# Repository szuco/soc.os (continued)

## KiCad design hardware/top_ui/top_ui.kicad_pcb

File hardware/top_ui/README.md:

# TOP – Front / UI

KiCad-Projekt `top_ui`. Bedien- und Sensorikebene des Stacks, zur Front orientiert.

## Umfang

Bestückt sind 29 Bauteile, 53 Netze (`bom_top.csv`):

- **USB-C-Buchse, stehend** (G-Switch GT-USB-7051x, vertikal SMT) — zeigt nach
  vorn und liegt unter der Zentralscheibe, mit **USBLC6-2SC6** als ESD-Schutz
  und 2 × 5k1 Rd
- **Runddisplay ST77916**, 1,46", 360 × 360, QSPI — über eine Steckerleiste;
  der Footprint ist ein **Platzhalter**, bis das reale Modul mit seinem FPC
  vermessen ist
- **Vier SMD-Taster** auf (±18 · ±20), exakt unter den Druckkreuzen der
  Zentralscheibe. Einzeln bedeuten sie nichts — jede Bedienrichtung ist ein
  Paar benachbarter Ecken, aufgelöst in der Firmware
- **SHT40-AD1B** (0x44) für Temperatur und Feuchte, thermisch über Schlitze
  entkoppelt
- **VL53L1X** als Präsenz- und Durchstiegssensor hinter dem **oberen** Steg
  (12 Uhr), XSHUT über 10k dauerhaft aktiv
- **Stern-Ausgang** über P-FET-High-Side und 0,2-A-PTC auf eine
  2,5-mm-Klinkenbuchse im **unteren** Steg (6 Uhr, Footprint noch Platzhalter,
  Punkt 30)
- `J7` als **unbestückte Reserve-UART** für ein späteres Satellitenmodul
- Stackverbinder `J_STK_A` und `J_STK_B` nach unten

Ein USB-UART-Baustein entfällt — der ESP32-S3 hat nativen USB (Punkt 24).

## Kernregeln

- **USB `D+`/`D−` laufen durch den Stack** (`J_STK_A` 34/36, benachbart, PGND
  daneben). Das ist die Regeländerung v0.3 in
  [`docs/03-stack-pinout.md`](../../docs/03-stack-pinout.md): Mit dem nativen USB
  des ESP32-S3 auf dem **Mid**-Board gibt es keine Alternative, und Full-Speed-USB
  über zwei benachbarte Kontakte ist unkritisch.
- ESD-Schutz unmittelbar an der USB-C-Buchse, `D+`/`D−` kurz führen.
- USB-C bleibt **Device/UFP**: `CC1` und `CC2` jeweils einzeln mit 5,1 kΩ Rd nach GND.
- Der Stern-Ausgang wird aus `6V2_STAR` über den Stack versorgt und leuchtet damit nur im
  24-V-Normalbetrieb — **nicht** aus USB-VBUS speisen.

## Mechanik

- **47 × 47 mm mit R 4**, 1,0 mm Dicke — als einziges Board nicht rund
- Bohrbild und Stackverbinder-Positionen **deckungsgleich** mit BOTTOM und MID
- Das Board ist **quadratisch, 47 × 47 mm mit R 4** — als einziges der drei.
  Es sitzt vor der Dose im Adapter, weil die Druckkreuze der Zentralscheibe auf
  r = 26,9 liegen und ein Kreis dort nicht hinreicht. Geometrie und Tiefenkette:
  [`mechanical/adapter.py`](../../mechanical/adapter.py)
- Frontorientierung: mathematisch +Y = „oben“, identisch auf allen drei Boards

Exakte Koordinaten: [`../../docs/04-mechanical.md`](../../docs/04-mechanical.md)

## Referenzdokumente

- [`docs/01-power-tree.md`](../../docs/01-power-tree.md) – USB-ORing, Stern-Versorgung
- [`docs/03-stack-pinout.md`](../../docs/03-stack-pinout.md) – Pinmapping
- [`docs/04-mechanical.md`](../../docs/04-mechanical.md) – Stern-Ausgang, Tiefenbudget
- [`docs/09-display-and-mcu.md`](../../docs/09-display-and-mcu.md) – Displaywahl, MCU, ToF
- [`docs/13-funktionsstatus.md`](../../docs/13-funktionsstatus.md) – Gesamtstand

## Status

Schaltplan erzeugt und netzlistengeprüft (`tools/gen_top_sch.py`, 29 Bauteile,
53 Netze).

**Layout: platziert, ohne Leiterbahnen.** Stand vom 15.08.2026, an diesem Tag
zweimal neu erzeugt:

1. **J1 stand um 180° verdreht** (Punkt 39) — die Stecköffnung zeigte zur
   Platinenmitte, die Lötpads standen über die Kante, sechs Bohrungen schnitten
   die Ø-52-Kontur an. Korrigiert: das engste Pad liegt jetzt 3,2 mm innerhalb
   der Kontur, die Randabstandsverletzungen sind von 11 auf 1 gefallen.
2. **Klinke und ToF getauscht**: Die Klinkenbuchse sitzt jetzt im **unteren**
   Steg (6 Uhr, mittig), der ToF allein im **oberen** (12 Uhr). Die USB-C-Buchse
   musste dafür von 6 nach 12 Uhr weichen und liegt links neben dem ToF; der
   unbestückte Reserve-UART J7 ist nach innen gerückt.

Die verbliebene Randabstandsverletzung gehört dem **Platzhalter**-Footprint der
Klinkenbuchse: Der 3,5-mm-Typ ist 14,4 mm lang, sein Bund sitzt in der Mitte —
bei einem Lochabstand von r = 22,5 steht das hintere Ende 3,3 mm über die
Platinenkante. Das reale 2,5-mm-Teil muss deutlich kleiner sein, siehe Punkt 30.

**Zwei Footprints sind Platzhalter** und vor der Bestellung zu ersetzen:
die Displaystiftleiste (Punkt 15c) und die Klinkenbuchse (Punkt 30, 3,5 mm
vertikal statt der gewollten 2,5 mm). Beides sind reale Bauteilmaße, die am
gekauften Teil zu nehmen sind — nicht aus einem Katalog.

**Nicht geprüft:** Schaltungsreview gegen Datenblätter.

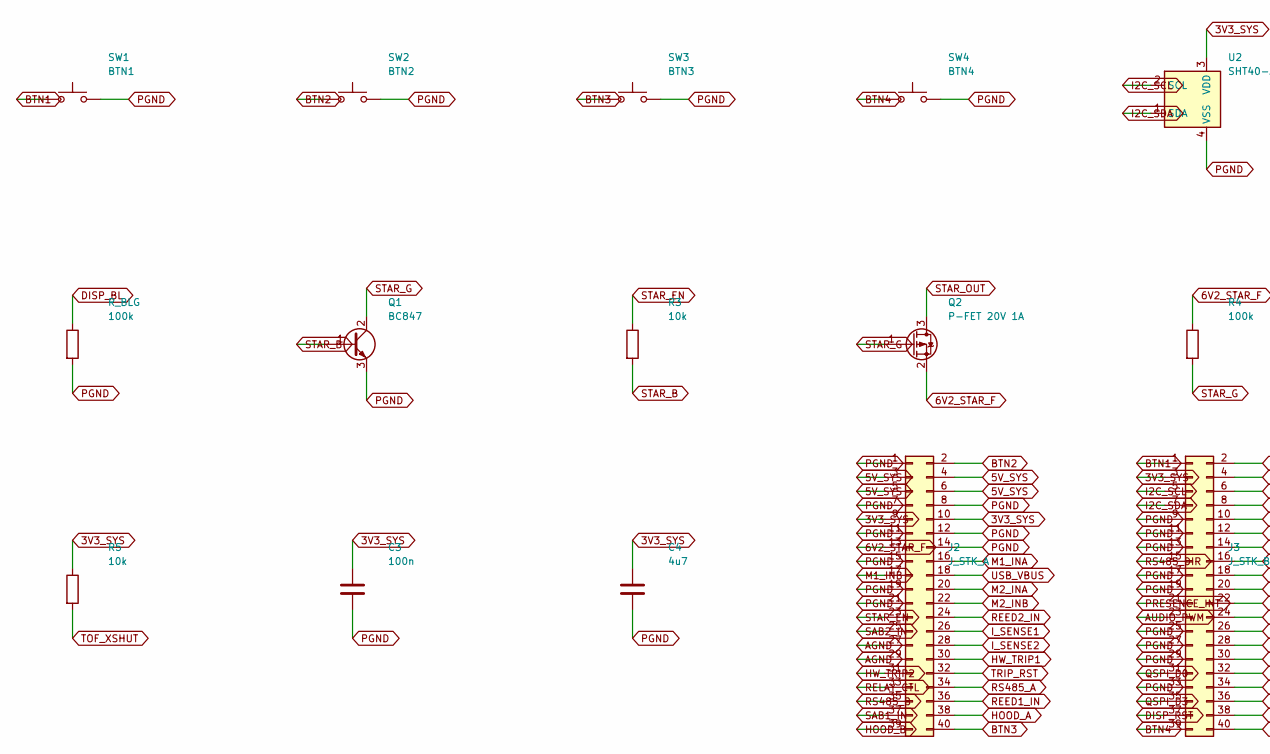
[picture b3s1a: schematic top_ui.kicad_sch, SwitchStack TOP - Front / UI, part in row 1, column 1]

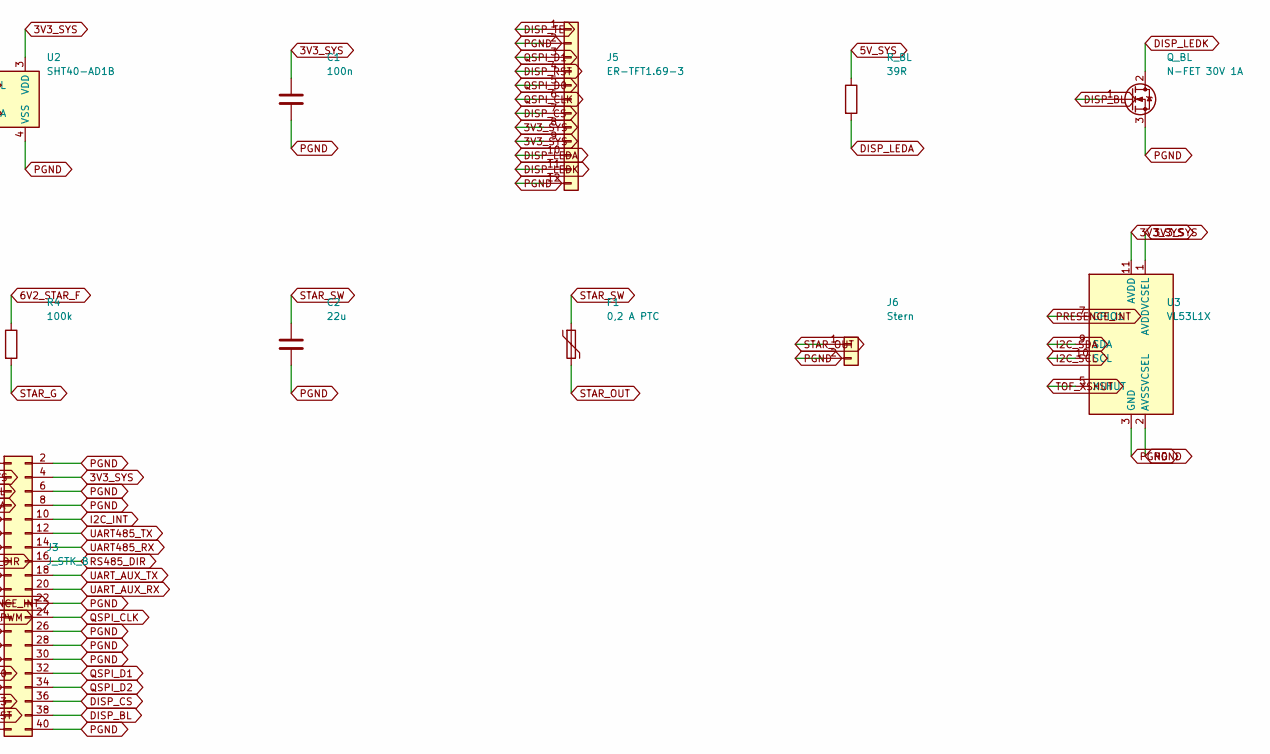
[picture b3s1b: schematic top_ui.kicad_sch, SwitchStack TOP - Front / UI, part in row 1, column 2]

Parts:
C1, C3: 100n; C_0603_1608Metric
C2: 22u; C_1210_3225Metric
C4: 4u7; C_0603_1608Metric
F1: 0,2 A PTC; Fuse_1206_3216Metric; MPN Haltestrom > 100 mA, Ausloesestrom < 40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
J2: J_STK_A; PinSocket_2x20_P1.27mm_Vertical
J3: J_STK_B; PinSocket_2x20_P1.27mm_Vertical
J5: ER-TFT1.69-3; TE_1-1734839-2_1x12-1MP_P0.5mm_Horizontal; MPN Panel ER-TFT1.69-3, 12-pol FPC 0,50 mm 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
J6: Stern; JST_GH_BM02B-GHS-TBT_1x02-1MP_P1.25mm_Vertical; MPN JST GH BM02B-GHS-TBT, 2-polig stehend m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
Q1: BC847; SOT-23
Q2: P-FET 20V 1A; SOT-23; MPN z.B. AO3401 - 80 mA Last, unkritisch
Q_BL: N-FET 30V 1A; SOT-23; MPN Logic-Level, Vgs(th) < 2 V - 2N7002 rei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
R3: 10k; R_0603_1608Metric
R4: 100k; R_0603_1608Metric; MPN Gate-Pull-up: aus ohne Ansteuerung
R5: 10k; R_0603_1608Metric; MPN XSHUT-Pullup: Sensor immer aktiv
R_BL: 39R; R_0603_1608Metric; MPN Vorwiderstand Hintergrundbeleuchtung, 8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
R_BLG: 100k; R_0603_1608Metric; MPN Gate-Pulldown: Beleuchtung aus, solange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
SW1: BTN1; SW_Push_SPST_NO_Alps_SKRK; MPN Alps SKRK o.ae., 3,9x2,9 - Ecke oben re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
SW2: BTN2; SW_Push_SPST_NO_Alps_SKRK; MPN Alps SKRK o.ae., 3,9x2,9 - Ecke oben li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
SW3: BTN3; SW_Push_SPST_NO_Alps_SKRK; MPN Alps SKRK o.ae., 3,9x2,9 - Ecke unten l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
SW4: BTN4; SW_Push_SPST_NO_Alps_SKRK; MPN Alps SKRK o.ae., 3,9x2,9 - Ecke unten r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
U2: SHT40-AD1B; Sensirion_DFN-4_1.5x1.5mm_P0.8mm_SHT4x_NoCentralPad; MPN Adresse 0x44 - muss zur YAML passen; th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
U3: VL53L1X; ST_VL53L1x; MPN Optikfenster freihalten, Uebersprechen: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

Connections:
3V3_SYS: C1.1, C3.1, C4.1, J2.9, J2.10, J3.3, J3.4, J5.8, J5.9, R5.1, U2.3 (VDD), U3.1 (AVDDVCSEL), U3.11 (AVDD)
5V_SYS: J2.3, J2.4, J2.5, J2.6, R_BL.1
6V2_STAR_F: J2.13, Q2.2 (S), R4.1
AGND: J2.27, J2.29
AUDIO_PWM: J3.23
BTN1: J3.1, SW1.1
BTN2: J2.2, SW2.1
BTN3: J2.40, SW3.1
BTN4: J3.39, SW4.1
DISP_BL: J3.38, Q_BL.1 (G), R_BLG.1
DISP_CS: J3.36, J5.7
DISP_LEDA: J5.10, R_BL.2
DISP_LEDK: J5.11, Q_BL.2 (D)
DISP_RST: J3.37, J5.4
DISP_TE: J5.1
HOOD_A: J2.38
HOOD_B: J2.39
HW_TRIP1: J2.30
HW_TRIP2: J2.31
I2C_INT: J3.10
I2C_SCL: J3.5, U2.2 (SCL), U3.10 (SCL)
I2C_SDA: J3.7, U2.1 (SDA), U3.9 (SDA)
I_SENSE1: J2.26
I_SENSE2: J2.28
M1_INA: J2.16
M1_INB: J2.17
M2_INA: J2.20
M2_INB: J2.22
PRESENCE_INT: J3.21, U3.7 (GPIO1)
QSPI_CLK: J3.24, J5.6
QSPI_D0: J3.31, J5.5
QSPI_D1: J3.32, J5.3
QSPI_D2: J3.34
QSPI_D3: J3.35
REED1_IN: J2.36
REED2_IN: J2.24
RELAY_CTL: J2.33
RS485_A: J2.34
RS485_B: J2.35
RS485_DIR: J3.15, J3.16
SAB1_IN: J2.37
SAB2_IN: J2.25
STAR_B: Q1.1 (B), R3.2
STAR_EN: J2.23, R3.1
STAR_G: Q1.2 (C), Q2.1 (G), R4.2
STAR_OUT: F1.2, J6.1, Q2.3 (D)
STAR_SW: C2.1, F1.1
TOF_XSHUT: R5.2, U3.5 (XSHUT)
TRIP_RST: J2.32
UART485_RX: J3.14
UART485_TX: J3.12
UART_AUX_RX: J3.20
UART_AUX_TX: J3.18
USB_VBUS: J2.18

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
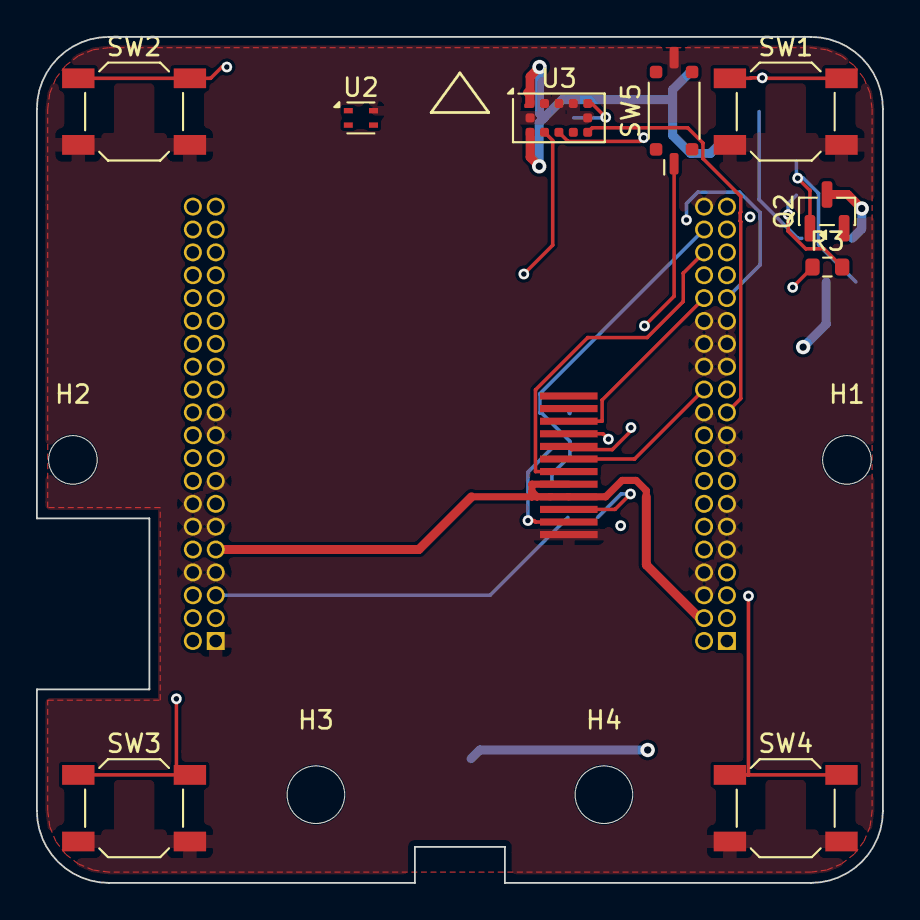
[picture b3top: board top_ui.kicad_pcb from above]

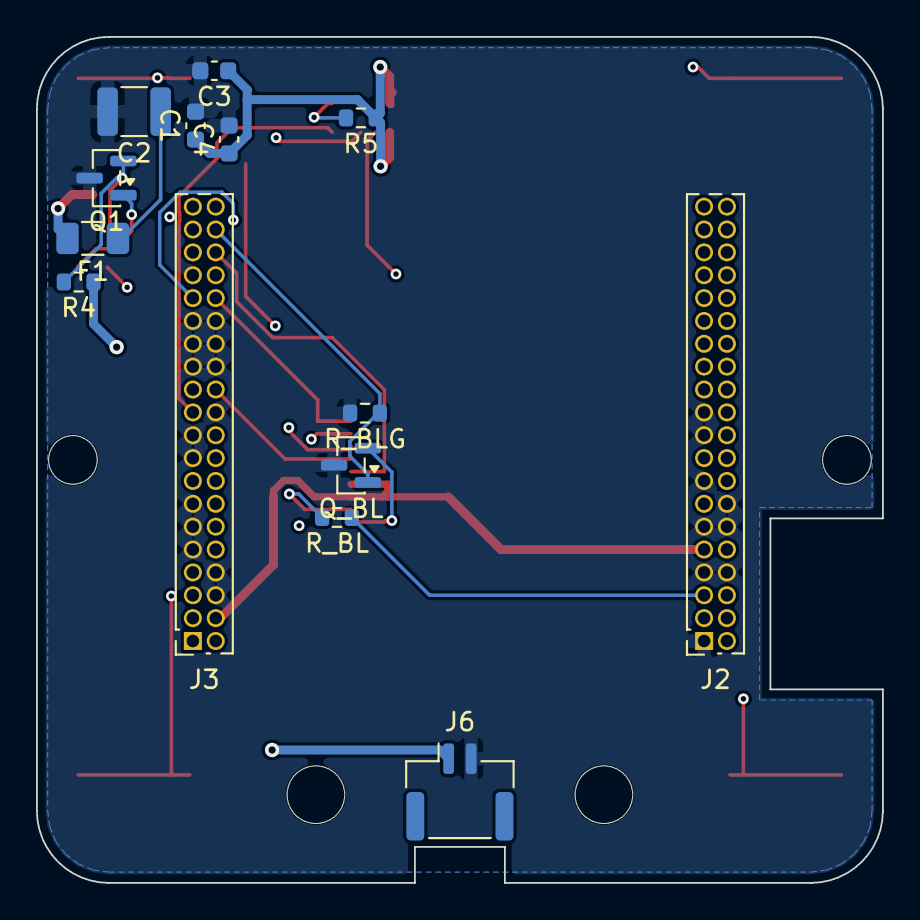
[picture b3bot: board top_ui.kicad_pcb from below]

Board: 4 copper layers, 47.0 x 47.0 mm, 28 parts (14 on the bottom side), 28 nets.

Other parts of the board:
H1, H2: MountingHole_2.7mm_M2.5
H3, H4: MountingHole_3.2mm_M3
SW5: HAUPT; SW_DIP_SPSTx01_Slide_Copal_CVS-01xB_W5.9mm_P1mm

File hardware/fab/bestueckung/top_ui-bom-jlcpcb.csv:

Comment,Designator,Footprint,LCSC Part #
"0,2 A PTC",F1,Fuse_1206_3216Metric,C207035
100k,"R4,R_BLG",R_0603_1608Metric,C25803
100n,"C1,C3",C_0603_1608Metric,C14663
10k,"R3,R5",R_0603_1608Metric,C25804
22u,C2,C_1210_3225Metric,C52306
39R,R_BL,R_0603_1608Metric,
4u7,C4,C_0603_1608Metric,C19666
BC847,Q1,SOT-23,C181141
BTN1,SW1,SW_SPST_SKQG_WithStem,C115351
BTN2,SW2,SW_SPST_SKQG_WithStem,C115351
BTN3,SW3,SW_SPST_SKQG_WithStem,C115351
BTN4,SW4,SW_SPST_SKQG_WithStem,C115351
ER-TFT1.69-3,J5,FPC_Loetfeld_12x0.7mm,
HAUPT,SW5,SW_DIP_SPSTx01_Slide_Copal_CVS-01xB_W5.9mm_P1mm,
J_STK_A,J2,PinSocket_2x20_P1.27mm_Vertical,
J_STK_B,J3,PinSocket_2x20_P1.27mm_Vertical,
N-FET 30V 1A,Q_BL,SOT-23,C20917
P-FET 20V 1A,Q2,SOT-23,C15127
SHT40-AD1B,U2,Sensirion_DFN-4_1.5x1.5mm_P0.8mm_SHT4x_NoCentralPad,C2909890
Stern (intern),J6,JST_GH_SM02B-GHS-TB_1x02-1MP_P1.25mm_Horizontal,C189893
VL53L1X,U3,ST_VL53L1x,

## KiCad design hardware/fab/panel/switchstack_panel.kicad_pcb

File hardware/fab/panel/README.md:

# Fertigungsnutzen

> **Gemischte Geometrie seit dem 16.08.2026.** Bottom und Mid sind Kreise
> Ø 52, das Top-Board ist ein abgerundetes Quadrat 47 × 47 (Punkt 48). Der
> Generator behandelt beide Formen: die Kreise über die Bogenlogik, das Quadrat
> über eine Parallelkurve seiner Kontur. **173,4 × 64,4 mm = 112 cm²**, vier
> Stege je Platine.

`switchstack_panel.kicad_pcb` enthält alle drei Platinen in einer Datei —
Bottom, Mid und Top nebeneinander, gehalten von Trennstegen in einem Rahmen.

> **Erzeugt, nicht gezeichnet.** Diese Datei ist ein Build-Ergebnis wie die
> Gerber. Sie wird nie von Hand bearbeitet, sondern neu erzeugt:
>
> ```bash
> /Applications/KiCad/KiCad.app/Contents/Frameworks/Python.framework/Versions/3.9/bin/python3 \
>     tools/gen_panel.py
> ```
>
> Änderungen gehören in die drei Quellprojekte unter `hardware/`. Der Nutzen
> greift beim nächsten Lauf darauf zu.

## Warum überhaupt ein Nutzen

KiCad kennt nur ein Board je Projekt — das Handbuch zu 10.0 ist da eindeutig:
*„a project can only contain a single board."* Wer die drei Platinen in einer
Datei will, hat zwei Möglichkeiten: die Quellen verschmelzen, oder einen Nutzen
erzeugen. Das Verschmelzen kostet die Referenzbezeichner (alles müsste ein
Präfix bekommen) und die Möglichkeit, ein Board allein zu revidieren. Der
erzeugte Nutzen kostet nichts davon: Bauteil- und Netznamen bekommen ihr Präfix
erst hier drin, wo Eindeutigkeit gefordert ist.

| Ebene | Präfix Referenz | Präfix Netz |
|---|---|---|
| Bottom | `B_` | `BOT_` |
| Mid | `M_` | `MID_` |
| Top | `T_` | `TOP_` |

## Geometrie

| | |
|---|---|
| Nutzengröße | **178,4 × 64,4 mm** (115 cm²) |
| Anordnung | drei Kreise Ø 52,0 in einer Reihe, Teilung 57,0 mm |
| Fräsfuge | 2,2 mm (Fräser 2,0 mm plus Toleranz) |
| Rahmen | 4,0 mm ringsum |
| Stege | 4 je Platine, 4,0 mm breit, auf den Diagonalen |
| Mausbisse | 5 × Ø 0,6 mm je Steg, 0,45 mm außerhalb der Platinenkante |

Die Reihe ist die flächengünstigste Anordnung: 115 cm² gegenüber 129 cm² beim
Dreieck (zwei oben, eine unten). Unter 100 × 100 mm ist nichts zu holen — drei
Kreise Ø 52 brauchen mathematisch mindestens ein Quadrat von 102 mm
Kantenlänge, und das ohne jede Trennfuge.

Die Stege liegen auf den **Diagonalen**, weil alle vier Achsrichtungen belegt
sind: 0° und 180° sind die Befestigungsbohrungen, 90° ist beim Top-Board der
überstehende USB-C-Stecker, 270° beim Mid-Board der Antennen-Keepout.

## Trennen — das ist Handarbeit

Runde Platinen lassen sich nicht ritzen. Nach dem Ausbrechen steht am Steg ein
Grat von etwa **0,5 mm** über. Der muss verputzt werden, bevor die Platine in
die Dose geht: Ø 52 in einer Dose mit 55–57 mm lichter Weite lässt 1,5–2,5 mm
Luft, ein unbearbeiteter Nub kann davon die Hälfte fressen.

Die Perforation liegt bewusst **außerhalb** der Platinenkante. Genau auf der
Kante würde jede Bohrung in den Randabstand des Kupfers ragen — das waren im
ersten Entwurf 480 zusätzliche Clearance-Fehler. Der Preis dafür ist genau
dieser Grat.

## Designregeln

Ohne eigene Projektdatei fiele der Nutzen auf KiCads Standardwerte zurück und
meldete Fehler, die keine sind — das Bottom-Board ist mit 0,15 mm Clearance
geroutet, die Vorgabe lautet 0,2 mm. `gen_panel.py` erzeugt deshalb auch
`switchstack_panel.kicad_pro` und überträgt die Regeln aus den drei
Quellprojekten: jede Ebene behält über ein Netzklassenmuster (`BOT_*`, `MID_*`,
`TOP_*`) ihre eigenen Werte, die Mindestvorgaben werden zur durchlässigsten
Variante zusammengefasst.

## Stand der Prüfung

Neu erzeugt am 15.08.2026, nachdem das Top-Board umgebaut wurde (Klinke auf
6 Uhr, ToF auf 12 Uhr, USB-C-Drehung korrigiert). Der DRC des Nutzens ist
**deckungsgleich mit der Summe der Einzelboards**:

| Klasse | Anzahl | Was dahintersteckt |
|---|---:|---|
| `clearance` | 28 | Pad-zu-Pad **innerhalb** des USB-C-Footprints: 0,85 mm Raster gegen 0,15 mm Vorgabe. Eine Regel-gegen-Footprint-Frage, kein Layoutfehler |
| `copper_edge_clearance` | 2 | Platzhalter-Footprint der Klinkenbuchse (Punkt 30) |
| `unconnected_items` | 342 | erwartet: **Mid und Top tragen keine Leiterbahnen**, Bottom ist zu ≈ 85 % geroutet, und die Masseflächen werden erst beim Öffnen in KiCad gefüllt |

Was der Nutzen **zusätzlich** meldet, sind Silkscreen-Überlappungen: durch die
Präfixe werden die Bezeichner länger. Das ist kosmetisch und betrifft keine
Kupferlage.

**Vor der Bestellung:** Mid und Top routen, Masseflächen füllen, DRC auf null
Kupferfehler bringen und die Fertigungsanweisung um das Verputzen der Stege
ergänzen.

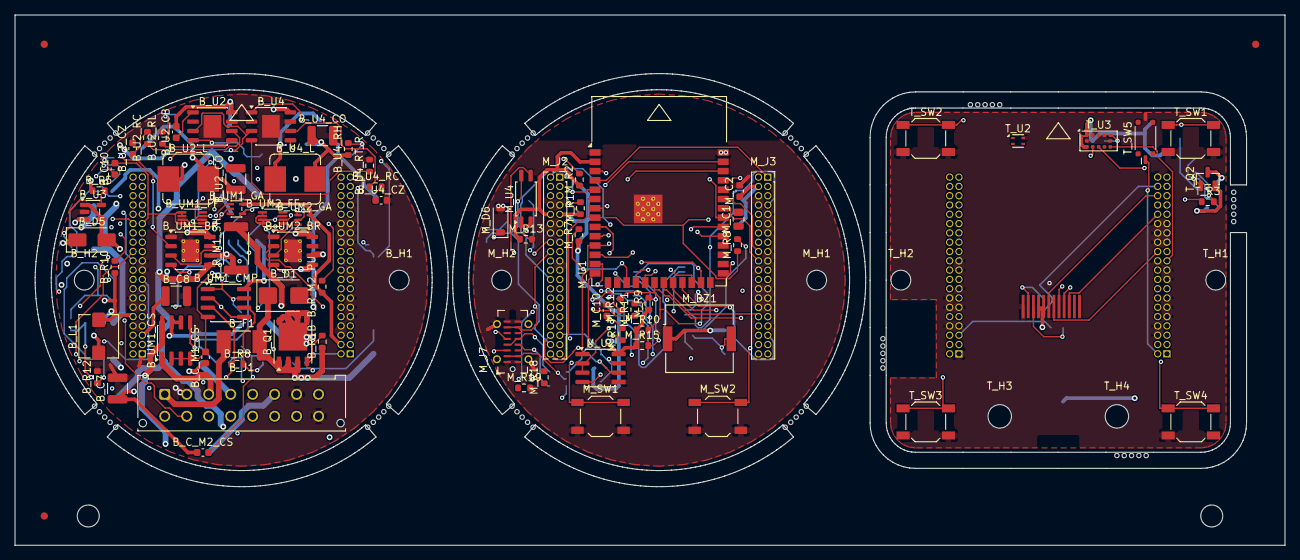
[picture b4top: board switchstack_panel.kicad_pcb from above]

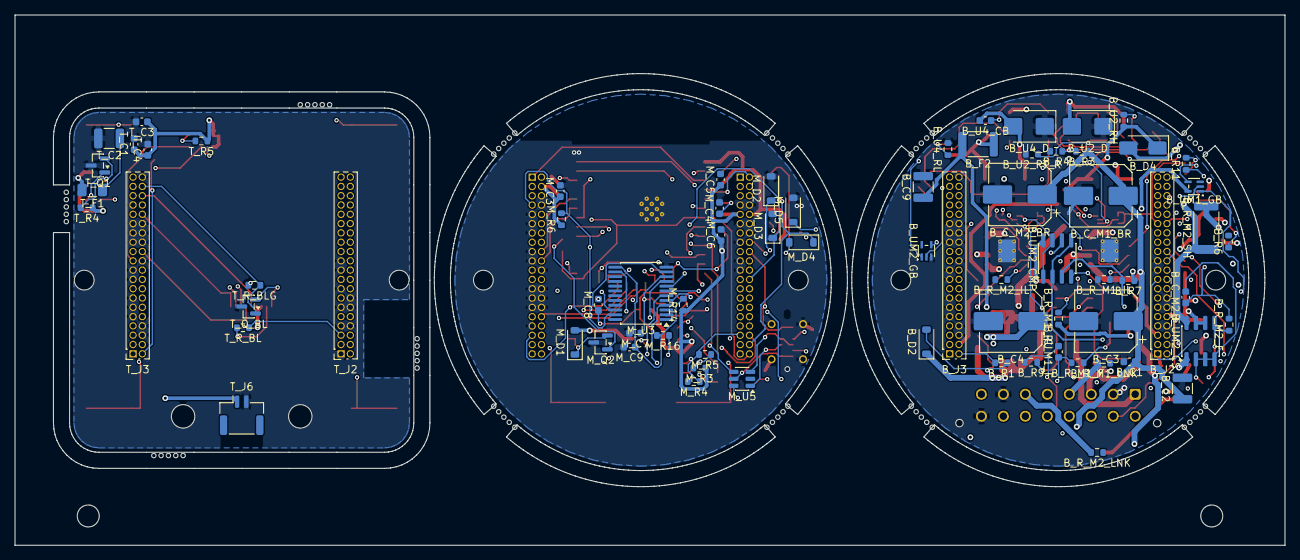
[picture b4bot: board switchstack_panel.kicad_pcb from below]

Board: 4 copper layers, 173.4 x 72.4 mm, 224 parts (74 on the bottom side), 155 nets.

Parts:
B_C1, B_C10: 100n; C_0603_1608Metric
B_C2: 10u; C_1210_3225Metric
B_C3, B_C4: 220u/35V Polymer; CP_Elec_8x6.5
B_C7, B_C8, B_C9: 22u; C_1210_3225Metric
B_C_M1_BR, B_C_M2_BR: 100u/35V Polymer; CP_Elec_8x6.5
B_C_M1_CS, B_C_M2_CS: 100n; C_0603_1608Metric
B_C_M1_F, B_C_M2_F: 1n; C_0603_1608Metric
B_D1: SMBJ30A; D_SMB
B_D2: 12V; D_SOD-123
B_D4, B_D5: 40V 3A; D_SMA
B_F1: 15A flink; Fuse_Littelfuse-NANO2-451_453
B_F2: 0.5A; Fuse_1812_4532Metric
B_H1, B_H2: MountingHole_2.7mm_M2.5
B_J1: Feld 16p; Molex_Micro-Fit_3.0_43045-1612_2x08_P3.00mm_Vertical
B_J2: J_STK_A; PinSocket_2x20_P1.27mm_Vertical
B_J3: J_STK_B; PinSocket_2x20_P1.27mm_Vertical
B_L1: 2u2; L_Bourns_SRP5030T
B_Q1: P-FET 40V 30A; PowerPAK_SO-8_Single
B_R1, B_R10: 100k; R_0603_1608Metric
B_R1B: 1M; R_0603_1608Metric
B_R3: 392k; R_0603_1608Metric
B_R4: 88k7; R_0603_1608Metric
B_R5: 180k; R_0603_1608Metric
B_R6, B_R8: 40k2; R_0603_1608Metric
B_R7, B_R9: 10k0; R_0603_1608Metric
B_R11: 1k; R_0603_1608Metric
B_R12: 0R; R_0603_1608Metric
B_R_M1_F, B_R_M2_F: 1k; R_0603_1608Metric
B_R_M1_IL, B_R_M2_IL: 33k0; R_0603_1608Metric
B_R_M1_LNK, B_R_M2_LNK: 0R; R_0603_1608Metric
B_R_M1_PU, B_R_M2_PU: 10k; R_0603_1608Metric
B_R_M1_SH, B_R_M2_SH: 5m0 1W; R_2512_6332Metric
B_U2, B_U4: TPS54360; HSOP-8-1EP_3.9x4.9mm_P1.27mm_EP2.41x3.1mm
B_U2_CB, B_U4_CB: 100n; C_0603_1608Metric
B_U2_CO: 47u; C_1210_3225Metric
B_U2_CZ, B_U4_CZ: 3n3; C_0603_1608Metric
B_U2_D, B_U4_D: 60V 3A; D_SMB
B_U2_L: 10u; L_Bourns_SRP7028A_7.3x6.6mm
B_U2_RC, B_U4_RC: 10k; R_0603_1608Metric
B_U2_RH: 53k6; R_0603_1608Metric
B_U2_RL: 10k2; R_0603_1608Metric
B_U2_RT_R, B_U4_RT_R: 100k; R_0603_1608Metric
B_U3: TLV62569; SOT-23-5
B_U4_CO: 22u; C_1210_3225Metric
B_U4_L: 33u; L_Bourns_SRP7028A_7.3x6.6mm
B_U4_RH: 68k1; R_0603_1608Metric
B_U4_RL: 10k0; R_0603_1608Metric
B_UM1_BR, B_UM2_BR: DRV8871; HSOP-8-1EP_3.9x4.9mm_P1.27mm_EP2.41x3.1mm_ThermalVias
B_UM1_CMP, B_UM2_CMP: TLV3702; SOIC-8_3.9x4.9mm_P1.27mm
B_UM1_CS, B_UM2_CS: INA240A2; SOIC-8_3.9x4.9mm_P1.27mm
B_UM1_FF, B_UM2_FF: 74AUP1G74; VSSOP-8_2.3x2mm_P0.5mm
B_UM1_GA, B_UM1_GB, B_UM2_GA, B_UM2_GB: 74AHC1G08; SOT-353_SC-70-5
FID: (no value)
FID#2, FID#3: (no value)
MB: (no value)
MB#2, MB#3, MB#4, MB#5, MB#6, MB#7, MB#8, MB#9, MB#10, MB#11, MB#12, MB#13, MB#14, MB#15, MB#16, MB#17, MB#18, MB#19, MB#20, MB#21, MB#22, MB#23, MB#24, MB#25, MB#26, MB#27, MB#28, MB#29, MB#30, MB#31, MB#32, MB#33, MB#34, MB#35, MB#36, MB#37, MB#38, MB#39, MB#40, MB#41, MB#42, MB#43, MB#44, MB#45, MB#46, MB#47, MB#48, MB#49, MB#50, MB#51, MB#52, MB#53, MB#54, MB#55, MB#56, MB#57, MB#58, MB#59, MB#60: (no value)
M_BZ1: Piezo passiv SMD; Buzzer_Murata_PKMCS0909E
M_C1: 10u; C_0805_2012Metric
M_C2, M_C5, M_C6, M_C7, M_C8, M_C9, M_C10: 100n; C_0603_1608Metric
M_C3, M_C4: 1u; C_0603_1608Metric
M_D1: 40V; D_SOD-123
M_D2, M_D3, M_D5, M_D6: 5V6; D_SOD-123
M_D4: 33V; D_SOD-123
M_H1, M_H2: MountingHole_2.7mm_M2.5
M_J2: J_STK_A; PinSocket_2x20_P1.27mm_Vertical
M_J3: J_STK_B; PinSocket_2x20_P1.27mm_Vertical
M_J7: USB-C; USB_C_Receptacle_G-Switch_GT-USB-7051x
M_Q2: BC847; SOT-23
M_R1, M_R2, M_R9, M_R10, M_R14, M_R15: 10k; R_0603_1608Metric
M_R3, M_R4: 560R; R_0603_1608Metric
M_R5: 120R; R_0603_1608Metric
M_R6, M_R7: 4k7; R_0603_1608Metric
M_R8, M_R11, M_R12, M_R16, M_R17: 1k; R_0603_1608Metric
M_R13: 330R; R_0603_1608Metric
M_R18, M_R19: 5k1; R_0603_1608Metric
M_SW1: RESET; SW_SPST_TL3342
M_SW2: BOOT; SW_SPST_TL3342
M_U1: ESP32-S3-WROOM-1-N16R8; ESP32-S3-WROOM-1
M_U2: MAX3485; SOIC-8_3.9x4.9mm_P1.27mm
M_U3: PCF8575; SSOP-24_5.3x8.2mm_P0.65mm
M_U4: PhotoMOS 60V; SOP-4_4.4x2.6mm_P1.27mm
M_U5: USBLC6-2SC6; SOT-23-6
TOOL: (no value)
TOOL#2: (no value)
T_C1, T_C3: 100n; C_0603_1608Metric
T_C2: 22u; C_1210_3225Metric
T_C4: 4u7; C_0603_1608Metric
T_F1: 0,2 A PTC; Fuse_1206_3216Metric
T_H1, T_H2: MountingHole_2.7mm_M2.5
T_H3, T_H4: MountingHole_3.2mm_M3
T_J2: J_STK_A; PinSocket_2x20_P1.27mm_Vertical
T_J3: J_STK_B; PinSocket_2x20_P1.27mm_Vertical
T_J5: ER-TFT1.69-3; FPC_Loetfeld_12x0.7mm
T_J6: Stern (intern); JST_GH_SM02B-GHS-TB_1x02-1MP_P1.25mm_Horizontal
T_Q1: BC847; SOT-23
T_Q2: P-FET 20V 1A; SOT-23
T_Q_BL: N-FET 30V 1A; SOT-23
T_R3, T_R5: 10k; R_0603_1608Metric
T_R4: 100k; R_0603_1608Metric
T_R_BL: 39R; R_0603_1608Metric
T_R_BLG: 100k; R_0603_1608Metric
T_SW1: BTN1; SW_SPST_SKQG_WithStem
T_SW2: BTN2; SW_SPST_SKQG_WithStem
T_SW3: BTN3; SW_SPST_SKQG_WithStem
T_SW4: BTN4; SW_SPST_SKQG_WithStem
T_SW5: HAUPT; SW_DIP_SPSTx01_Slide_Copal_CVS-01xB_W5.9mm_P1mm
T_U2: SHT40-AD1B; Sensirion_DFN-4_1.5x1.5mm_P0.8mm_SHT4x_NoCentralPad
T_U3: VL53L1X; ST_VL53L1x

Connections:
BOT_3V3_SYS: B_C7.1, B_C_M1_CS.1, B_C_M2_CS.1, B_J2.9, B_J2.10, B_J3.3, B_J3.4, B_L1.2, B_R5.1, B_R7.1, B_R10.1, B_R_M1_PU.1, B_R_M2_PU.1, B_UM1_CMP.8, B_UM1_CS.6, B_UM1_CS.7, B_UM1_FF.8, B_UM1_GA.5, B_UM1_GB.5, B_UM2_CMP.8, B_UM2_CS.6, B_UM2_CS.7, B_UM2_FF.8, B_UM2_GA.5, B_UM2_GB.5
BOT_5V_BUCK: B_D4.1, B_U2_CO.1, B_U2_L.2, B_U2_RH.1
BOT_5V_SYS: B_C8.1, B_D4.2, B_D5.2, B_J2.3, B_J2.4, B_J2.5, B_J2.6, B_U3.1, B_U3.4
BOT_6V2_STAR: B_F2.1, B_U4_CO.1, B_U4_L.2, B_U4_RH.1
BOT_6V2_STAR_F: B_C9.1, B_F2.2, B_J2.13
BOT_24V_EN: B_R3.2, B_R4.1, B_U2.3, B_U4.3
BOT_24V_F: B_D1.1, B_D2.1, B_F1.2, B_Q1.1, B_Q1.2, B_Q1.3, B_R1B.1
BOT_24V_GATE_P: B_D2.2, B_Q1.4, B_R1.1, B_R1B.2
BOT_24V_IN: B_F1.1, B_J1.1
BOT_24V_PROT: B_C1.1, B_C2.1, B_C3.1, B_C4.1, B_C_M1_BR.1, B_C_M2_BR.1, B_Q1.5, B_R3.1, B_U2.2, B_U4.2, B_UM1_BR.5, B_UM2_BR.5
BOT_AGND: B_C10.2, B_C_M1_CS.2, B_C_M1_F.2, B_C_M2_CS.2, B_C_M2_F.2, B_J2.27, B_J2.29, B_R9.2, B_R12.1, B_UM1_CMP.4, B_UM1_CS.2, B_UM1_CS.3, B_UM1_CS.4, B_UM1_FF.1, B_UM1_FF.2, B_UM1_FF.4, B_UM2_CMP.4, B_UM2_CS.2, B_UM2_CS.3, B_UM2_CS.4, B_UM2_FF.1, B_UM2_FF.2, B_UM2_FF.4
BOT_EN_LOOP: B_J3.2, B_R1.2
BOT_HOOD_A: B_J1.14, B_J2.38
BOT_HOOD_B: B_J1.15, B_J2.39
BOT_HW_TRIP1: B_J2.30, B_UM1_FF.5
BOT_HW_TRIP2: B_J2.31, B_UM2_FF.5
BOT_I_SENSE1: B_C_M1_F.1, B_J2.26, B_R_M1_F.2
BOT_I_SENSE2: B_C_M2_F.1, B_J2.28, B_R_M2_F.2
BOT_M1_A: B_J1.3, B_R_M1_SH.2, B_UM1_CS.1
BOT_M1_B: B_J1.4, B_R_M1_LNK.2, B_UM1_BR.8
BOT_M1_GA: B_UM1_BR.3, B_UM1_GA.4
BOT_M1_GB: B_UM1_BR.2, B_UM1_GB.4
BOT_M1_ILIM: B_R_M1_IL.1, B_UM1_BR.4
BOT_M1_INA: B_J2.16, B_UM1_GA.1
BOT_M1_INB: B_J2.17, B_UM1_GB.1
BOT_M1_ISNS: B_R_M1_F.1, B_UM1_CMP.2, B_UM1_CMP.5, B_UM1_CS.5
BOT_M1_SD: B_UM1_FF.3, B_UM1_GA.2, B_UM1_GB.2
BOT_M1_SWA: B_R_M1_SH.1, B_UM1_BR.6, B_UM1_CS.8
BOT_M1_TRIP: B_R_M1_PU.2, B_UM1_CMP.1, B_UM1_CMP.7, B_UM1_FF.7
BOT_M2_A: B_J1.5, B_R_M2_SH.2, B_UM2_CS.1
BOT_M2_B: B_J1.6, B_R_M2_LNK.2, B_UM2_BR.8
BOT_M2_GA: B_UM2_BR.3, B_UM2_GA.4
BOT_M2_GB: B_UM2_BR.2, B_UM2_GB.4
BOT_M2_ILIM: B_R_M2_IL.1, B_UM2_BR.4
BOT_M2_INA: B_J2.20, B_UM2_GA.1
BOT_M2_INB: B_J2.22, B_UM2_GB.1
BOT_M2_ISNS: B_R_M2_F.1, B_UM2_CMP.2, B_UM2_CMP.5, B_UM2_CS.5
BOT_M2_SD: B_UM2_FF.3, B_UM2_GA.2, B_UM2_GB.2
BOT_M2_SWA: B_R_M2_SH.1, B_UM2_BR.6, B_UM2_CS.8
BOT_M2_TRIP: B_R_M2_PU.2, B_UM2_CMP.1, B_UM2_CMP.7, B_UM2_FF.7
BOT_PGND: B_C1.2, B_C2.2, B_C3.2, B_C4.2, B_C7.2, B_C8.2, B_C9.2, B_C_M1_BR.2, B_C_M2_BR.2, B_D1.2, B_J1.2, B_J1.7, B_J1.16, B_J2.1, B_J2.7, B_J2.8, B_J2.11, B_J2.12, B_J2.14, B_J2.15, B_J2.19, B_J2.21, B_J3.6, B_J3.8, B_J3.9, B_J3.11, B_J3.13, B_J3.17, B_J3.19, B_J3.22, B_J3.25, B_J3.26, B_J3.27, B_J3.28, B_J3.29, B_J3.30, B_J3.33, B_J3.40, B_R4.2, B_R6.2, B_R12.2, B_R_M1_IL.2, B_R_M2_IL.2, B_U2.7, B_U2.9, B_U2_CO.2, B_U2_CZ.2, B_U2_D.1, B_U2_RL.2, B_U2_RT_R.2, B_U3.2, B_U4.7, B_U4.9, B_U4_CO.2, B_U4_CZ.2, B_U4_D.1, B_U4_RL.2, B_U4_RT_R.2, B_UM1_BR.1, B_UM1_BR.7, B_UM1_BR.9, B_UM1_GA.3, B_UM1_GB.3, B_UM2_BR.1, B_UM2_BR.7, B_UM2_BR.9, B_UM2_GA.3, B_UM2_GB.3
BOT_REED1_IN: B_J1.10, B_J2.36
BOT_REED2_IN: B_J1.12, B_J2.24
BOT_RS485_A: B_J1.8, B_J2.34
BOT_RS485_B: B_J1.9, B_J2.35
BOT_RS485_DIR: B_J3.15, B_J3.16
BOT_SAB1_IN: B_J1.11, B_J2.37
BOT_SAB2_IN: B_J1.13, B_J2.25
BOT_TRIP_CLR: B_C10.1, B_R10.2, B_R11.2, B_UM1_FF.6, B_UM2_FF.6
BOT_TRIP_RST: B_J2.32, B_R11.1
BOT_U2_BOOT: B_U2.1, B_U2_CB.1
BOT_U2_COMP: B_U2.6, B_U2_RC.1
BOT_U2_CZ_N: B_U2_CZ.1, B_U2_RC.2
BOT_U2_FB: B_U2.5, B_U2_RH.2, B_U2_RL.1
BOT_U2_RT: B_U2.4, B_U2_RT_R.1
BOT_U2_SW: B_U2.8, B_U2_CB.2, B_U2_D.2, B_U2_L.1
BOT_U3_FB: B_R5.2, B_R6.1, B_U3.5
BOT_U3_SW: B_L1.1, B_U3.3
BOT_U4_BOOT: B_U4.1, B_U4_CB.1
BOT_U4_COMP: B_U4.6, B_U4_RC.1
BOT_U4_CZ_N: B_U4_CZ.1, B_U4_RC.2
BOT_U4_FB: B_U4.5, B_U4_RH.2, B_U4_RL.1
BOT_U4_RT: B_U4.4, B_U4_RT_R.1
BOT_U4_SW: B_U4.8, B_U4_CB.2, B_U4_D.2, B_U4_L.1
BOT_USB_VBUS: B_D5.1, B_J2.18
BOT_V_TRIP_HI: B_R7.2, B_R8.1, B_UM1_CMP.3, B_UM2_CMP.3
BOT_V_TRIP_LO: B_R8.2, B_R9.1, B_UM1_CMP.6, B_UM2_CMP.6
MID_3V3_SYS: M_C1.1, M_C2.1, M_C3.1, M_C5.1, M_C6.1, M_J2.9, M_J2.10, M_J3.3, M_J3.4, M_R1.1, M_R2.1, M_R3.1, M_R6.1, M_R7.1, M_R9.1, M_R10.1, M_R13.1, M_R14.1, M_R15.1, M_U1.2, M_U2.8, M_U3.24
MID_5V_SYS: M_BZ1.1, M_D1.2, M_J2.3, M_J2.4, M_J2.5, M_J2.6
MID_AGND: M_J2.27, M_J2.29
MID_AUDIO_B: M_Q2.1, M_R8.2
MID_AUDIO_LOW: M_BZ1.2, M_D1.1, M_Q2.2
MID_AUDIO_PWM: M_J3.23, M_R8.1, M_U1.8
MID_BTN1: M_J3.1, M_U1.4
MID_BTN2: M_J2.2, M_U1.5
MID_BTN3: M_J2.40, M_U1.6
MID_BTN4: M_J3.39, M_U1.7
MID_DISP_BL: M_J3.38, M_U1.37
MID_DISP_CS: M_J3.36, M_U1.18
MID_DISP_RST: M_J3.37, M_U1.9
MID_ESP_BOOT: M_R2.2, M_SW2.1, M_U1.27
MID_ESP_EN: M_C4.1, M_R1.2, M_SW1.1, M_U1.3
MID_EXP_P6: M_C7.1, M_R9.2, M_R11.2, M_U3.10
MID_EXP_P7: M_C8.1, M_R10.2, M_R12.2, M_U3.11
MID_EXP_P8: M_C9.1, M_R14.2, M_R16.2, M_U3.13
MID_EXP_P9: M_C10.1, M_R15.2, M_R17.2, M_U3.14
MID_HOOD_A: M_D4.1, M_J2.38, M_U4.4
MID_HOOD_B: M_D4.2, M_J2.39, M_U4.3
MID_HW_TRIP1: M_J2.30, M_U3.4
MID_HW_TRIP2: M_J2.31, M_U3.5
MID_I2C_SCL: M_J3.5, M_R7.2, M_U1.17, M_U3.22
MID_I2C_SDA: M_J3.7, M_R6.2, M_U1.12, M_U3.23
MID_I_SENSE1: M_J2.26, M_U1.39
MID_I_SENSE2: M_J2.28, M_U1.38
MID_M1_INA: M_J2.16, M_U1.31
MID_M1_INB: M_J2.17, M_U1.32
MID_M2_INA: M_J2.20, M_U1.33
MID_M2_INB: M_J2.22, M_U1.24
MID_PGND: M_C1.2, M_C2.2, M_C3.2, M_C4.2, M_C5.2, M_C6.2, M_C7.2, M_C8.2, M_C9.2, M_C10.2, M_D2.2, M_D3.2, M_D5.2, M_D6.2, M_J2.1, M_J2.7, M_J2.8, M_J2.11, M_J2.12, M_J2.14, M_J2.15, M_J2.19, M_J2.21, M_J3.6, M_J3.8, M_J3.9, M_J3.11, M_J3.13, M_J3.17, M_J3.19, M_J3.22, M_J3.25, M_J3.26, M_J3.27, M_J3.28, M_J3.29, M_J3.30, M_J3.33, M_J3.40, M_J7.A1, M_J7.A12, M_J7.B1, M_J7.B12, M_J7.SH, M_Q2.3, M_R4.2, M_R18.2, M_R19.2, M_SW1.2, M_SW2.2, M_U1.1, M_U1.40, M_U1.41, M_U2.5, M_U3.2, M_U3.3, M_U3.12, M_U3.21, M_U5.2
MID_PRESENCE_INT: M_J3.21, M_U3.8
MID_QSPI_CLK: M_J3.24, M_U1.20
MID_QSPI_D0: M_J3.31, M_U1.19
MID_QSPI_D1: M_J3.32, M_U1.21
MID_QSPI_D2: M_J3.34, M_U1.22
MID_QSPI_D3: M_J3.35, M_U1.23
MID_REED1_IN: M_D2.1, M_J2.36, M_R11.1
MID_REED2_IN: M_D3.1, M_J2.24, M_R12.1
MID_RELAY_CTL: M_J2.33, M_U3.9, M_U4.2
MID_RELAY_LED: M_R13.2, M_U4.1
MID_RS485_A: M_J2.34, M_R3.2, M_R5.1, M_U2.6
MID_RS485_B: M_J2.35, M_R4.1, M_R5.2, M_U2.7
MID_RS485_DIR: M_J3.15, M_J3.16, M_U1.25, M_U2.2, M_U2.3
MID_SAB1_IN: M_D5.1, M_J2.37, M_R16.1
MID_SAB2_IN: M_D6.1, M_J2.25, M_R17.1
MID_STAR_EN: M_J2.23, M_U3.7
MID_TRIP_RST: M_J2.32, M_U3.6
MID_UART485_RX: M_J3.14, M_U1.11, M_U2.1
MID_UART485_TX: M_J3.12, M_U1.10, M_U2.4
MID_UART_AUX_RX: M_J3.20, M_U1.34
MID_UART_AUX_TX: M_J3.18, M_U1.35
MID_USB_CC1: M_J7.A5, M_R18.1
MID_USB_CC2: M_J7.B5, M_R19.1
MID_USB_DN: M_U1.13, M_U5.6
MID_USB_DN_C: M_J7.A7, M_J7.B7, M_U5.1
MID_USB_DP: M_U1.14, M_U5.4
MID_USB_DP_C: M_J7.A6, M_J7.B6, M_U5.3
MID_USB_VBUS: M_J2.18, M_J7.A4, M_J7.A9, M_J7.B4, M_J7.B9, M_U5.5
TOP_3V3_SYS: T_C1.1, T_C3.1, T_C4.1, T_J2.9, T_J2.10, T_J3.3, T_J3.4, T_J5.8, T_J5.9, T_R5.1, T_U2.3, T_U3.1, T_U3.11
TOP_5V_SYS: T_J2.3, T_J2.4, T_J2.5, T_J2.6, T_R_BL.1
TOP_6V2_STAR_F: T_J2.13, T_Q2.2, T_R4.1
TOP_AGND: T_J2.27, T_J2.29
TOP_BTN1: T_J3.1, T_SW1.1
TOP_BTN2: T_J2.2, T_SW2.1
TOP_BTN3: T_J2.40, T_SW3.1
TOP_BTN4: T_J3.39, T_SW4.1
TOP_DISP_BL: T_J3.38, T_Q_BL.1, T_R_BLG.1
TOP_DISP_CS: T_J3.36, T_J5.7
TOP_DISP_LEDA: T_J5.10, T_R_BL.2
TOP_DISP_LEDK: T_J5.11, T_Q_BL.2
TOP_DISP_RST: T_J3.37, T_J5.4
TOP_EN_LOOP: T_J3.2, T_SW5.1
TOP_I2C_SCL: T_J3.5, T_U2.2, T_U3.10
TOP_I2C_SDA: T_J3.7, T_U2.1, T_U3.9
TOP_PGND: T_C1.2, T_C2.2, T_C3.2, T_C4.2, T_J2.1, T_J2.7, T_J2.8, T_J2.11, T_J2.12, T_J2.14, T_J2.15, T_J2.19, T_J2.21, T_J3.6, T_J3.8, T_J3.9, T_J3.11, T_J3.13, T_J3.17, T_J3.19, T_J3.22, T_J3.25, T_J3.26, T_J3.27, T_J3.28, T_J3.29, T_J3.30, T_J3.33, T_J3.40, T_J5.2, T_J5.12, T_J6.2, T_Q1.3, T_Q_BL.3, T_R_BLG.2, T_SW1.2, T_SW2.2, T_SW3.2, T_SW4.2, T_SW5.2, T_U2.4, T_U3.2, T_U3.3, T_U3.4, T_U3.6, T_U3.12
TOP_PRESENCE_INT: T_J3.21, T_U3.7
TOP_QSPI_CLK: T_J3.24, T_J5.6
TOP_QSPI_D0: T_J3.31, T_J5.5
TOP_QSPI_D1: T_J3.32, T_J5.3
TOP_RS485_DIR: T_J3.15, T_J3.16
TOP_STAR_B: T_Q1.1, T_R3.2
TOP_STAR_EN: T_J2.23, T_R3.1
TOP_STAR_G: T_Q1.2, T_Q2.1, T_R4.2
TOP_STAR_OUT: T_F1.2, T_J6.1, T_Q2.3
TOP_STAR_SW: T_C2.1, T_F1.1
TOP_TOF_XSHUT: T_R5.2, T_U3.5

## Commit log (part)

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2022-01-18 Test
